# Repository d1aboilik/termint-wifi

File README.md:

# termint-wifi
This board allows the user to establish wireless terminal connection by reaching an internal RS-232 header over WiFi, using ESP8266 &amp; MAX3232.

## Description
Low-level console access to manage your x86 server can be very useful, and several motherboards offer internal and external RS-232 ports for this purpose. While these are very simple and reliable, we do not want to play around with serial cables and their adapters all the time, to attach our client devices. This is where termint-wifi comes in, making one of your internal serial ports WiFi-ready, granting a convenient way to accomplish server management. It can provide a solid backup path if mounted and wired up in the machine's chassis.

## Features
* Keeps the attached machine easily reachable even if it's network ports are down or misconfigured
* OS independent, and if your chipset supports it, you can manage your UEFI/BIOS over WiFi
* Client independent, you can use any WiFi capable device (e.g. smartphones, laptops, etc.)
* Code independent and upgradeable, you can upload any serial-to-wifi bridge solution, even your own
* Components are very cheap, and you have a few options to select the ESP8266 microcontroller
* Can be powered from microUSB or internal 12V source (recommended free fan header)
* Easily accessible pin headers for potential new features
* Made with THT and mostly superior SMD components, to allow soldering by hand with average tools
* Can link to non-x86 RS-232 capable devices as well

## Technical details

Microcontrollers are very smart nowadays, but RS-232 ports are still a bit difficult to handle, mostly due to voltage level. Because of this, the board uses MAX3232 line driver/receiver to make the connection, and the applied ESP8266 forwards the data from UART to WiFi interface. You can find the full schematic in the [KiCAD project.](kicad_board/)

| Termint-wifi 4-pin header | Motherboard pins |
| ---------- | ---- |
| RX | Internal RS-232 header TXD |
| TX | Internal RS-232 header RXD | 
| GND | Internal RS-232 header GND | 
| VIN | Optional, any 12V pin (recommended free fan header) | 

| Applicable code | Tested |
| ---------- | ---- |
| [ESPTerm](https://espterm.github.io/term.html) | Tested |
| [esp-link](https://github.com/jeelabs/esp-link) | Tested | 
| [ESPEasy](https://github.com/letscontrolit/ESPEasy) | Tested | 

*Keep in mind you can only turn on MAX3232 from code, by setting GPIO5 HIGH. This prevents boot problems caused by pulling Wemos TX low too early.*

| Compatible ESP8266 boards | Tested |
| ---------- | ---- |
| Wemos D1 mini Pro V1.x (wemos, blue) | Tested |
| Wemos D1 mini Pro V2.x (lolin, green) | Not tested | 
| Wemos D1 mini | Not tested | 
| Wemos D1 mini Lite | Not tested | 

*Models with external antenna are recommended, if the board is mounted inside chassis.*

## PCB BOM
The following components are needed to assemble the pcb:

| Component  | Type | Package | Value | Quantity |
| ---------- | ---- | ------- | ----- | -------- |
| R1 | Resistor | SMD-1206 | 100kΩ | 1 |
| R2 | Resistor | SMD-1206 | 10kΩ | 1 |
| R3 | Resistor | SMD-1206 | 130Ω | 1 |
| C1 | Tantalum capacitor | SMD-1206 | 10uF | 1 |
| C2-C6 | Capacitor | SMD-1206 | 100nF | 5 |
| Q1 | BJT Transistor | SOT-23 | MMBT3904 | 1 |
| Q2 | FET Transistor | SOT-23 | AO3401 | 1 |
| LED1 | LED | SMD-1206 | Vf=2V, If=10mA | 1 |
| LD1117 | Voltage regulator | SOT223 | LD1117S33TR | 1 |
| MAX3232 | RS232 Driver | SOIC16 | MAX3232IDR/IDRG4 | 1 |
| Pin socket | Connector | 2.54mm single row | 8-pin female | 2 |
| Pin header | Connector | 2.54mm single row | 8-pin male | 2 |
| Pin header, angled | Connector | 2.54mm single row | 4-pin male | 1 |

Additional parts:

| Component  | Type | Package | Quantity |
| ---------- | ---- | ------- | -------- |
| *Wemos D1 mini* | *ESP8266 board* | *Lite/Pro/Pro_V2* | *1* | 

## Assembly and application
1. Clone or download this repository.
2. Use the prebuilt [gerber archive](kicad_board/gerber/termint_wifi.zip) to print the pcb. Any chinese manufacturer (JLPCB, ALLPCB, PCBWAY, etc.) can fabricate a copy for a couple dollars. Really, it's dirt cheap.
3. Once you got the pcb and the few listed components, assemble termint-wifi by hand soldering, no special tool needed.
4. Upload the desired code (from the list or your own) to the selected Wemos using [esptool](https://github.com/espressif/esptool) or other similar software, and put it in the socket.
5. Mount the board in the target machine's chassis, wire up the listed connections, apply power.
6. Based on the code you use, connect over WiFi and test the access to your RS-232 port.

*The uploaded board fits perfectly on the side of an Antec ISK600M chassis. Resize the pcb in KiCAD as needed.*

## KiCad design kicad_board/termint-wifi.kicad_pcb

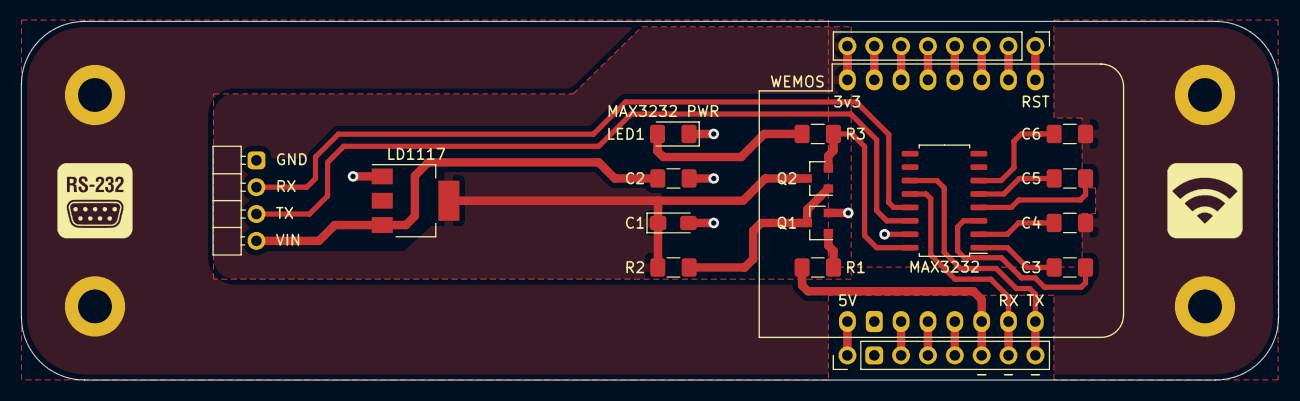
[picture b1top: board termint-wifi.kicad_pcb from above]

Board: 2 copper layers, 118.9 x 33.9 mm, 22 parts (0 on the bottom side), 29 nets.

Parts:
C1: 10uF; CP_EIA-3216-12_Kemet-S_Pad1.58x1.35mm_HandSolder
C2, C3, C4, C5, C6: 100nF; C_1206_3216Metric_Pad1.42x1.75mm_HandSolder
H1, H2, H3, H4: MountingHole_Pad; MountingHole_3.2mm_M3_ISO7380_Pad
J1: Conn_01x04_Male; PinHeader_1x04_P2.54mm_Horizontal
J2, J3: Conn_01x08; PinHeader_1x08_P2.54mm_Vertical
LD1117: LD1117S33TR_SOT223; SOT-223-3_TabPin2
LED1: LED; LED_1206_3216Metric_Pad1.42x1.75mm_HandSolder
MAX3232: MAX3232; SOIC-16_4.55x10.3mm_P1.27mm
Q1: MMBT3904; SOT-23
Q2: AO3401A; SOT-23
R1: 100k; R_1206_3216Metric_Pad1.42x1.75mm_HandSolder
R2: 10k; R_1206_3216Metric_Pad1.42x1.75mm_HandSolder
R3: 130R; R_1206_3216Metric_Pad1.42x1.75mm_HandSolder
WEMOS_D1: WeMos_D1_mini; WEMOS_D1_mini_light

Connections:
GND: C1.2, C2.2, C4.2, C6.2, H1.1, H2.1, H3.1, H4.1, J1.4, J3.2, LD1117.1, LED1.1, MAX3232.15, Q1.2, WEMOS_D1.10
unnamed: C1.1, J2.8, LD1117.2, Q2.3, R2.2, WEMOS_D1.8
unnamed: C2.1, J1.1, LD1117.3
unnamed: C3.1, MAX3232.1
unnamed: C3.2, MAX3232.3
unnamed: C4.1, MAX3232.2
unnamed: C5.1, MAX3232.4
unnamed: C5.2, MAX3232.5
unnamed: C6.1, MAX3232.6
unnamed: J1.2, MAX3232.14
unnamed: J1.3, MAX3232.13
unnamed: J2.1, WEMOS_D1.1
unnamed: J2.2, WEMOS_D1.2
unnamed: J2.3, WEMOS_D1.3
unnamed: J2.4, WEMOS_D1.4
unnamed: J2.5, WEMOS_D1.5
unnamed: J2.6, WEMOS_D1.6
unnamed: J2.7, WEMOS_D1.7
unnamed: J3.1, WEMOS_D1.9
unnamed: J3.3, WEMOS_D1.11
unnamed: J3.4, WEMOS_D1.12
unnamed: J3.5, WEMOS_D1.13
unnamed: J3.6, R1.2, WEMOS_D1.14
unnamed: J3.7, MAX3232.12, WEMOS_D1.15
unnamed: J3.8, MAX3232.11, WEMOS_D1.16
unnamed: LED1.2, R3.1
unnamed: MAX3232.16, Q2.2, R3.2
unnamed: Q1.1, R1.1
unnamed: Q1.3, Q2.1, R2.1

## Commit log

2020-06-03 Graphics & KiCAD board
2020-06-04 Updated logical illustration
2020-06-04 Updated component numbering
2020-06-04 Added gerber
2020-06-04 Changed capacitor package sizes
2020-06-04 Updated render
2020-06-04 Updated renders
2020-06-17 Major changes: -made max3232 switchable on GPIO5. This prevents boot problems due to Wemos TX pulling low, because you can only turn on MAX3232 from code, past boot sequence. -added max3232 power ind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
2020-06-17 Update gerber files
2020-06-17 Update renders
2020-06-17 Marked C1 polarity
